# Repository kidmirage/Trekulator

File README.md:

# Trekulator
A reproduction of the 1977 Star Trek themed calculator.

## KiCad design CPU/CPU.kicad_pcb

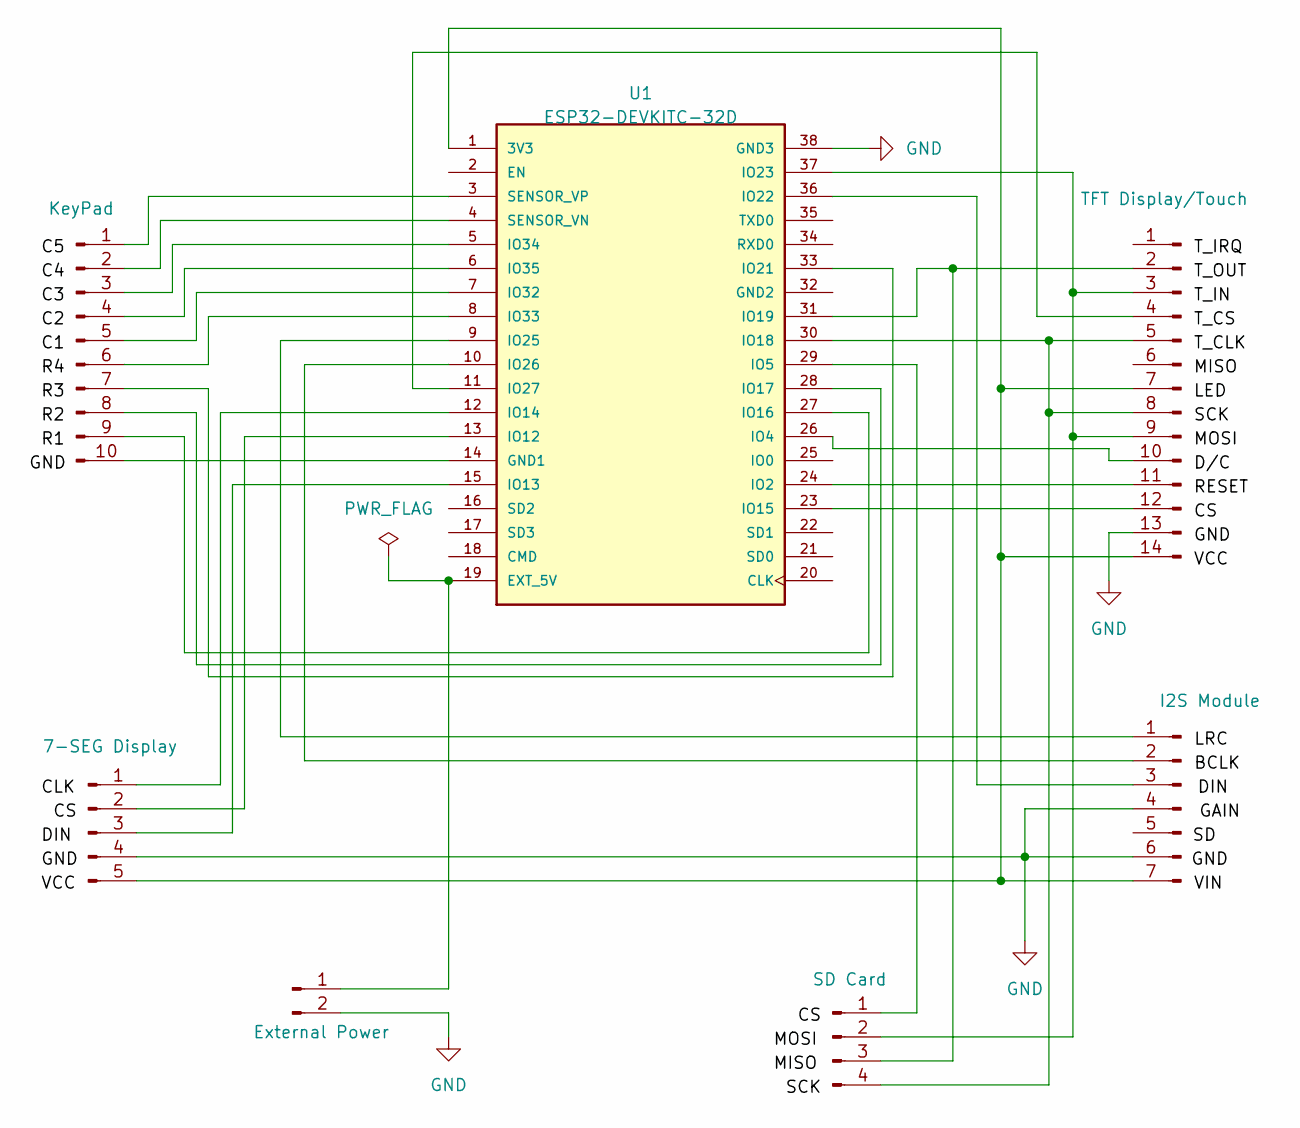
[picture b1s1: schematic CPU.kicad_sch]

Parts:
J1: TFT Display/Touch; PinHeader_1x14_P2.54mm_Vertical
J2: KeyPad; PinHeader_1x10_P2.54mm_Vertical
J3: SD Card; PinHeader_1x04_P2.54mm_Vertical
J4: 7-SEG Display; PinHeader_1x05_P2.54mm_Vertical
J5: I2S Module; PinHeader_1x07_P2.54mm_Vertical
J6: External Power; PinHeader_1x02_P2.54mm_Vertical
U1: ESP32-DEVKITC-32D; ESP32-DevKitC; PARTREV V4

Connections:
GND: J1.13, J4.4, J5.4, J5.6, J6.2, U1.38 (GND3)
unnamed: J1.2, J3.3, U1.31 (IO19)
unnamed: J1.3, J1.9, J3.2, U1.37 (IO23)
unnamed: J1.4, U1.11 (IO27)
unnamed: J1.5, J1.8, J3.4, U1.30 (IO18)
unnamed: J1.10, U1.26 (IO4)
unnamed: J1.11, U1.24 (IO2)
unnamed: J1.12, U1.23 (IO15)
unnamed: J1.7, J1.14, J4.5, J5.7, U1.1 (3V3)
unnamed: J2.1, U1.3 (SENSOR_VP)
unnamed: J2.2, U1.4 (SENSOR_VN)
unnamed: J2.3, U1.5 (IO34)
unnamed: J2.4, U1.6 (IO35)
unnamed: J2.5, U1.7 (IO32)
unnamed: J2.6, U1.8 (IO33)
unnamed: J2.7, U1.33 (IO21)
unnamed: J2.8, U1.28 (IO17)
unnamed: J2.9, U1.27 (IO16)
unnamed: J2.10, U1.14 (GND1)
unnamed: J3.1, U1.29 (IO5)
unnamed: J4.1, U1.12 (IO14)
unnamed: J4.2, U1.13 (IO12)
unnamed: J4.3, U1.15 (IO13)
unnamed: J5.1, U1.9 (IO25)
unnamed: J5.2, U1.10 (IO26)
unnamed: J5.3, U1.36 (IO22)
unnamed: J6.1, U1.19 (EXT_5V)

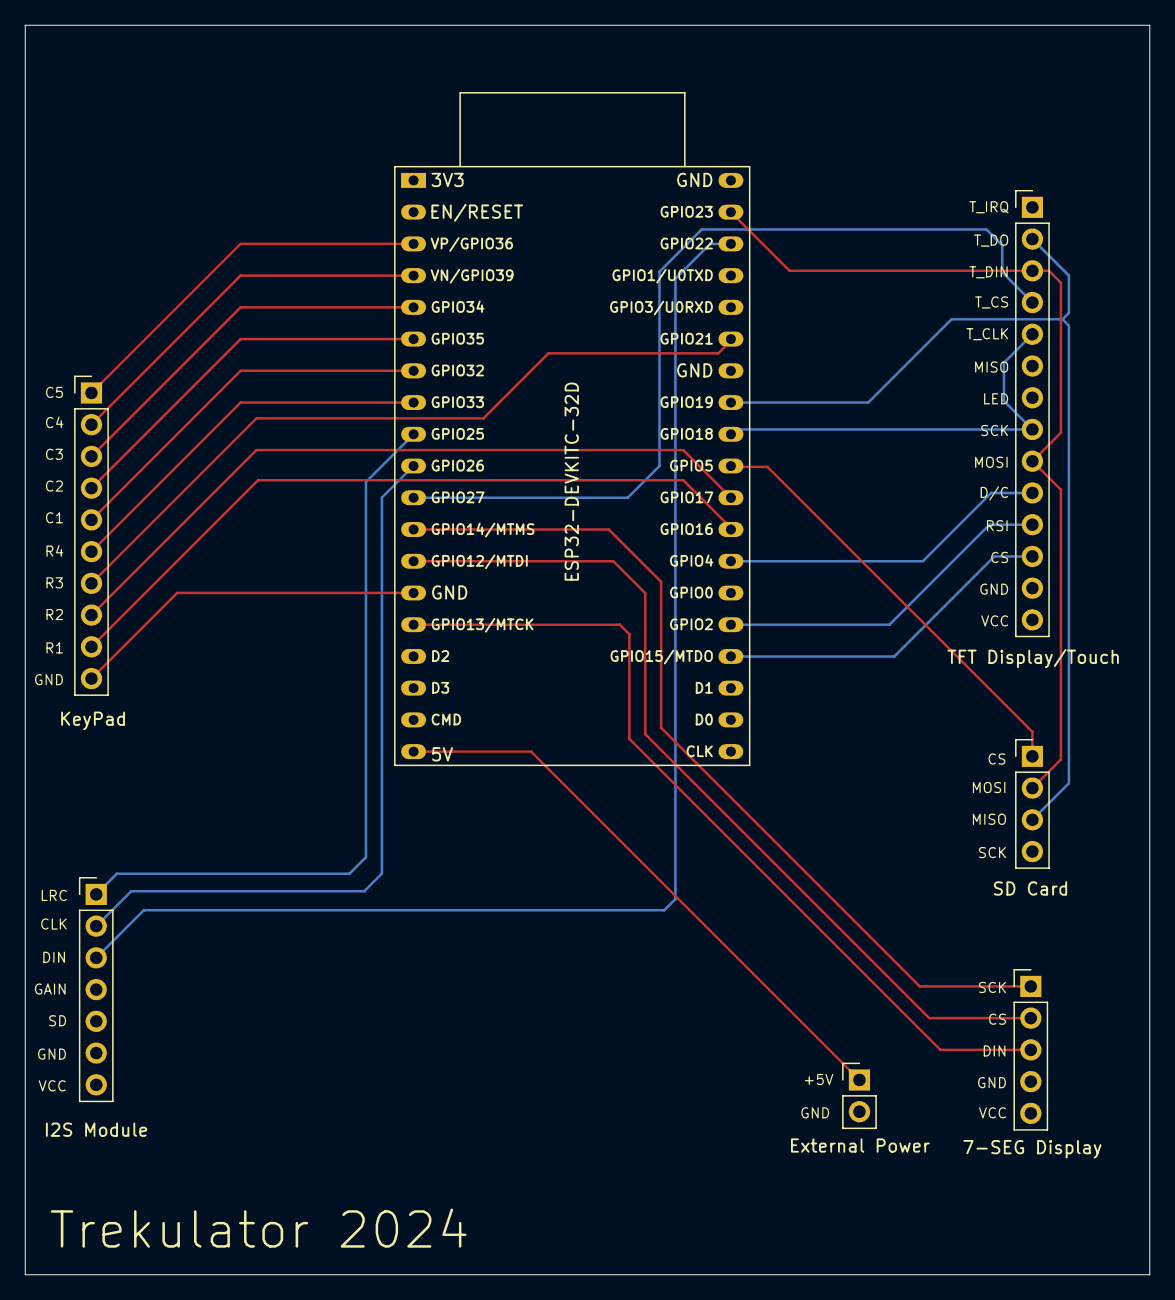
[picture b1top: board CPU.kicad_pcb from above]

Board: 4 copper layers, 90.0 x 100.0 mm, 7 parts (0 on the bottom side), 27 nets.

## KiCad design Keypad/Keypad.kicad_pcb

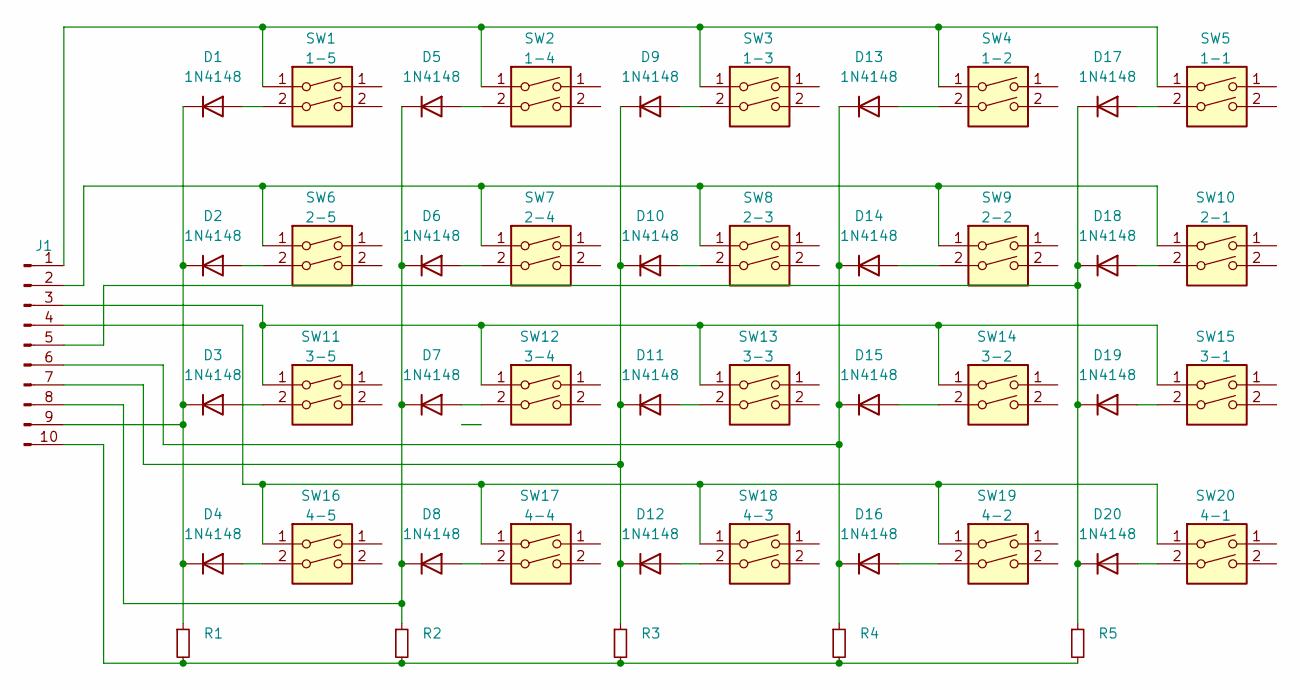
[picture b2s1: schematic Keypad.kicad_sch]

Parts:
D1, D2, D3, D4, D5, D6, D7, D8, D9, D10, D11, D12, D13, D14, D15, D16, D17, D18, D19, D20: 1N4148; D_DO-35_SOD27_P7.62mm_Horizontal
J1: Conn_01x10_Pin; PinHeader_1x10_P2.54mm_Vertical
R1, R2, R3, R4, R5: R_Small; R_Axial_DIN0207_L6.3mm_D2.5mm_P2.54mm_Vertical
SW1: 1-5; SW_PUSH-12mm_Wuerth-430476085716
SW2: 1-4; SW_PUSH-12mm_Wuerth-430476085716
SW3: 1-3; SW_PUSH-12mm_Wuerth-430476085716
SW4: 1-2; SW_PUSH-12mm_Wuerth-430476085716
SW5: 1-1; SW_PUSH-12mm_Wuerth-430476085716
SW6: 2-5; SW_PUSH-12mm_Wuerth-430476085716
SW7: 2-4; SW_PUSH-12mm_Wuerth-430476085716
SW8: 2-3; SW_PUSH-12mm_Wuerth-430476085716
SW9: 2-2; SW_PUSH-12mm_Wuerth-430476085716
SW10: 2-1; SW_PUSH-12mm_Wuerth-430476085716
SW11: 3-5; SW_PUSH-12mm_Wuerth-430476085716
SW12: 3-4; SW_PUSH-12mm_Wuerth-430476085716
SW13: 3-3; SW_PUSH-12mm_Wuerth-430476085716
SW14: 3-2; SW_PUSH-12mm_Wuerth-430476085716
SW15: 3-1; SW_PUSH-12mm_Wuerth-430476085716
SW16: 4-5; SW_PUSH-12mm_Wuerth-430476085716
SW17: 4-4; SW_PUSH-12mm_Wuerth-430476085716
SW18: 4-3; SW_PUSH-12mm_Wuerth-430476085716
SW19: 4-2; SW_PUSH-12mm_Wuerth-430476085716
SW20: 4-1; SW_PUSH-12mm_Wuerth-430476085716

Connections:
unnamed: D1.2 (A), SW1.2
unnamed: D1.1 (K), D2.1 (K), D3.1 (K), D4.1 (K), J1.9, R1.1
unnamed: D2.2 (A), SW6.2
unnamed: D3.2 (A), SW11.2
unnamed: D4.2 (A), SW16.2
unnamed: D5.2 (A), SW2.2
unnamed: D5.1 (K), D6.1 (K), D7.1 (K), D8.1 (K), J1.8, R2.1
unnamed: D6.2 (A), SW7.2
unnamed: D7.2 (A), SW12.2
unnamed: D8.2 (A), SW17.2
unnamed: D9.2 (A), SW3.2
unnamed: D10.2 (A), SW8.2
unnamed: D9.1 (K), D10.1 (K), D11.1 (K), D12.1 (K), J1.7, R3.1
unnamed: D11.2 (A), SW13.2
unnamed: D12.2 (A), SW18.2
unnamed: D13.2 (A), SW4.2
unnamed: D13.1 (K), D14.1 (K), D15.1 (K), D16.1 (K), J1.6, R4.1
unnamed: D14.2 (A), SW9.2
unnamed: D15.2 (A), SW14.2
unnamed: D16.2 (A), SW19.2
unnamed: D17.2 (A), SW5.2
unnamed: D17.1 (K), D18.1 (K), D19.1 (K), D20.1 (K), J1.5, R5.1
unnamed: D18.2 (A), SW10.2
unnamed: D19.2 (A), SW15.2
unnamed: D20.2 (A), SW20.2
unnamed: J1.1, SW1.1, SW2.1, SW3.1, SW4.1, SW5.1
unnamed: J1.2, SW6.1, SW7.1, SW8.1, SW9.1, SW10.1
unnamed: J1.3, SW11.1, SW12.1, SW13.1, SW14.1, SW15.1
unnamed: J1.4, SW16.1, SW17.1, SW18.1, SW19.1, SW20.1
unnamed: J1.10, R1.2, R2.2, R3.2, R4.2, R5.2

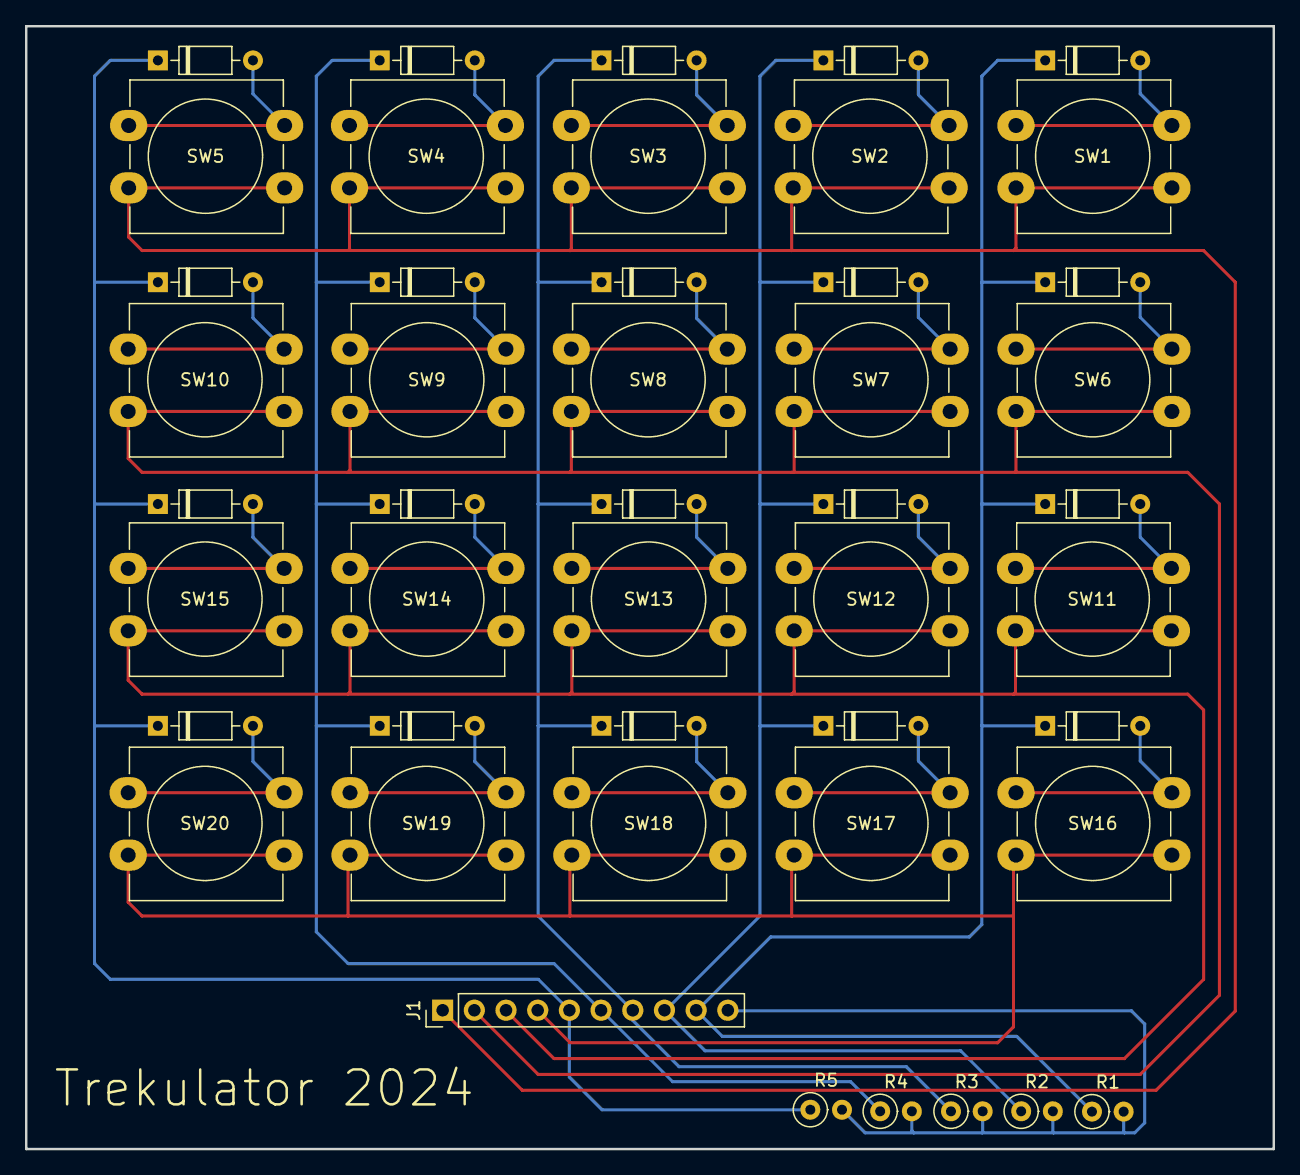
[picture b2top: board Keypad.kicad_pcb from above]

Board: 2 copper layers, 100.0 x 90.0 mm, 46 parts (0 on the bottom side), 30 nets.

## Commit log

2024-12-08 Add files via upload
    Working files and Gerbers for the Trekulator keypad.
2024-12-08 Add files via upload
    3D models for the Trekulator case.
2025-03-20 Add files via upload
    Added the Gerber files necessary to build the CPU board for Trekulator.
2025-03-20 Add files via upload
    Code for the Trekulator demo.
2025-05-02 Add files via upload
    Plate files for use with AMS equipped Bambu.
2025-05-15 Add files via upload
    Added Screen Mask.
2025-05-17 Add files via upload
    Added the files that go onto the SD Card.
2025-05-17 Add files via upload
    Remove references to SPIFF files.
2025-05-17 Add files via upload
    Add the default screen image.
2025-05-17 Add files via upload
    Added slide show images.
2025-05-18 Add files via upload
    Locking tab for the keypad and TFT display.
2025-05-18 Delete Models/Keypad Tabs.3mf
    Replaced with Locking Tab
